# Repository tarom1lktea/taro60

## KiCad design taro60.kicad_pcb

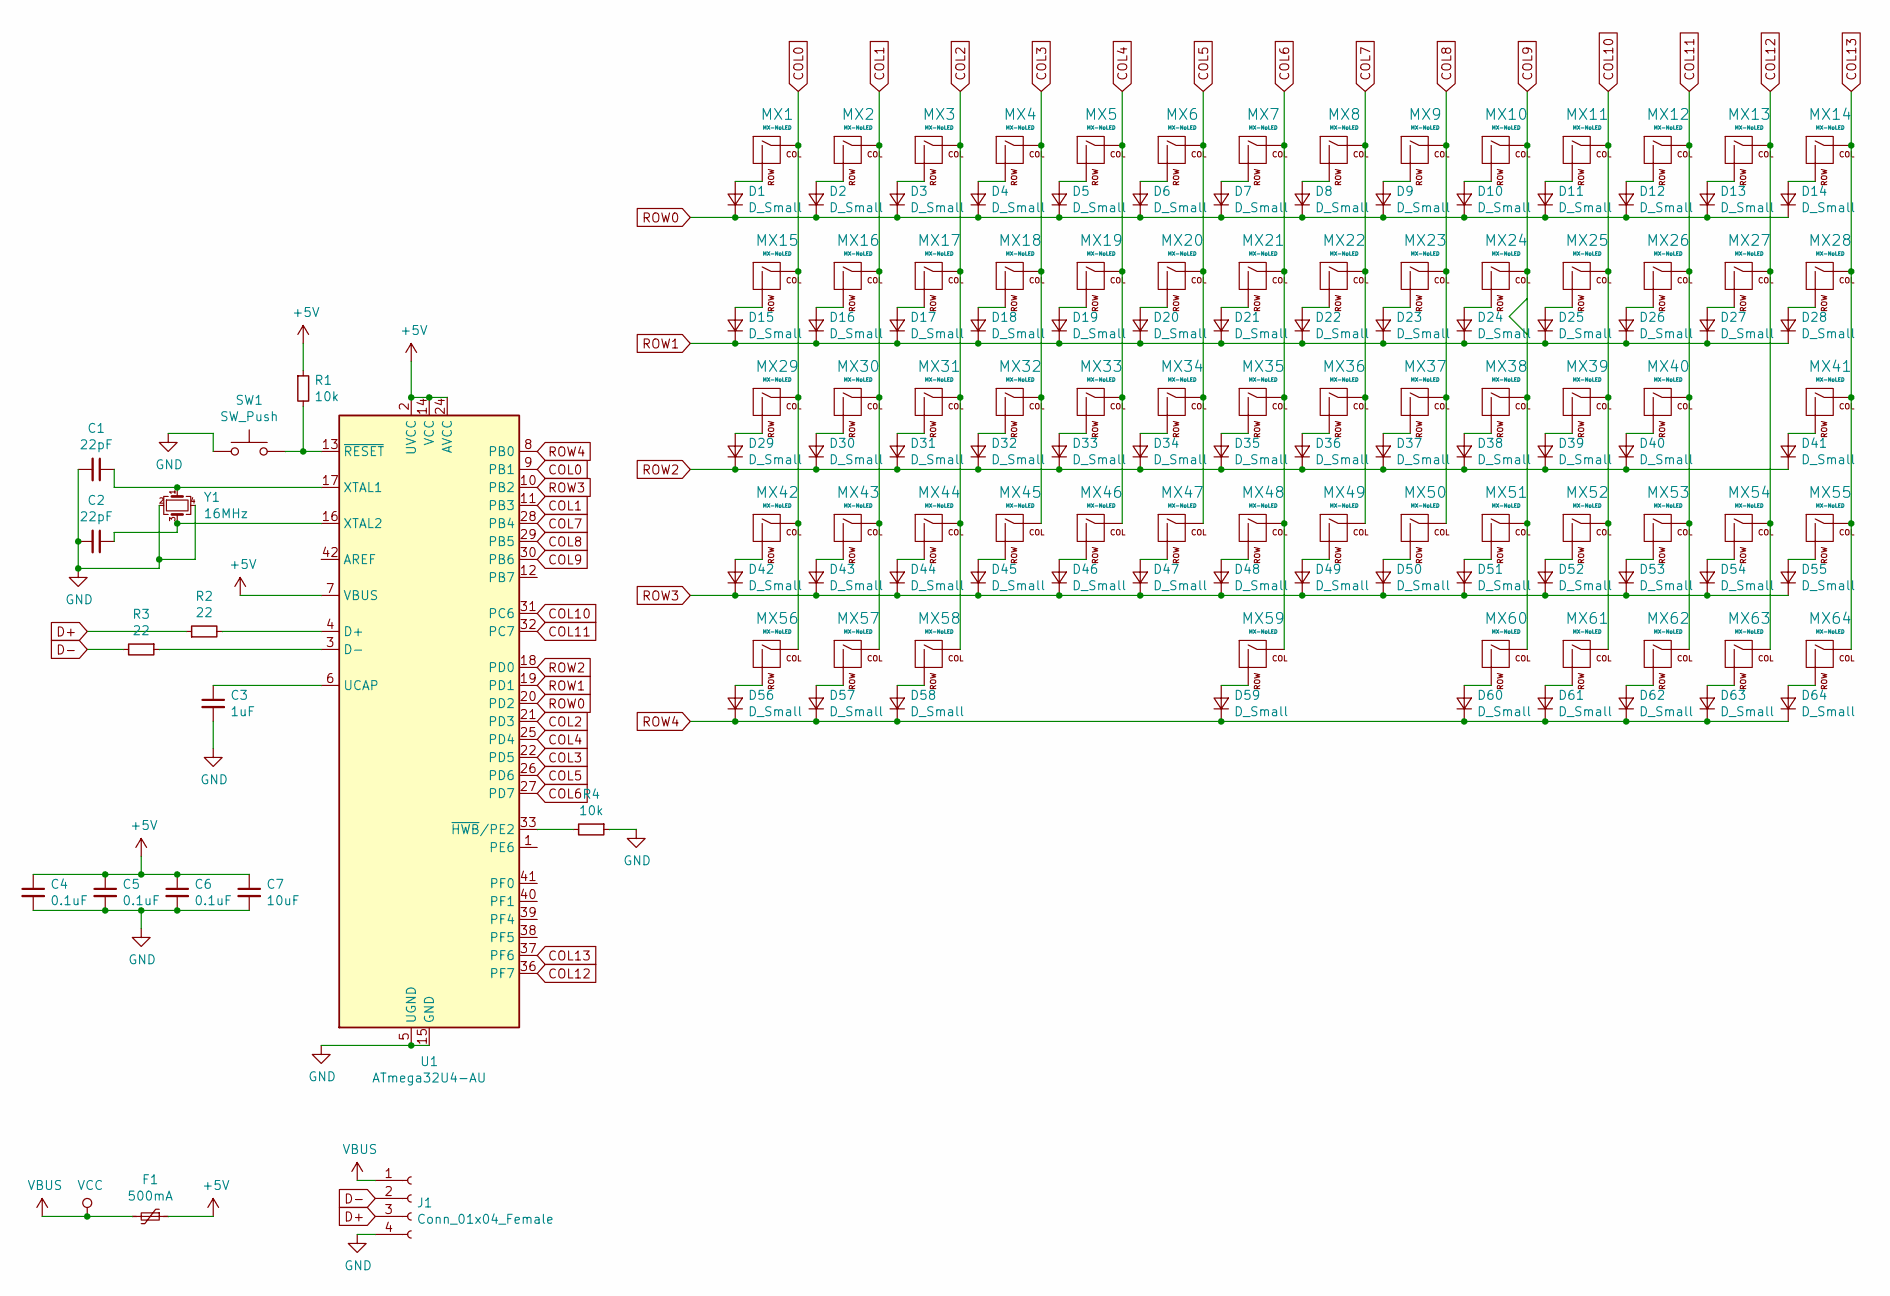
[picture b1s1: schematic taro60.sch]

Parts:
C1, C2: 22pF; C_0805_2012Metric
C3: 1uF; C_0805_2012Metric
C4, C5, C6: 0.1uF; C_0805_2012Metric
C7: 10uF; C_0805_2012Metric
D1, D2, D3, D4, D5, D6, D7, D8, D9, D10, D11, D12, D13, D14, D15, D16, D17, D18, D19, D20, D21, D22, D23, D24, D25, D26, D27, D28, D29, D30, D31, D32, D33, D34, D35, D36, D37, D38, D39, D40, D41, D42, D43, D44, D45, D46, D47, D48, D49, D50, D51, D52, D53, D54, D55, D56, D57, D58, D59, D60, D61, D62, D63, D64: D_Small; D_SOD-123
F1: 500mA; Fuse_1206_3216Metric
J1: Conn_01x04_Female; Molex_CLIK-Mate_502382-0470_1x04-1MP_P1.25mm_Vertical
MX1, MX2, MX3, MX4, MX5, MX6, MX7, MX8, MX9, MX10, MX11, MX12, MX13, MX16, MX17, MX18, MX19, MX20, MX21, MX22, MX23, MX24, MX25, MX26, MX27, MX30, MX31, MX32, MX33, MX34, MX35, MX36, MX37, MX38, MX39, MX40, MX43, MX44, MX45, MX46, MX47, MX48, MX49, MX50, MX51, MX52, MX53, MX54, MX55, MX60, MX61, MX62, MX63, MX64: MX-NoLED; MX-1U-NoLED
MX14, MX42: MX-NoLED; MX-2U-NoLED
MX15, MX28: MX-NoLED; MX-1.5U-NoLED
MX29: MX-NoLED; MX-1.75U-NoLED
MX41: MX-NoLED; MX-2.25U-NoLED
MX56, MX57, MX58: MX-NoLED; MX-1.25U-NoLED
MX59: MX-NoLED; MX-6.25U-ReversedStabilizers-NoLED
R1, R4: 10k; R_0805_2012Metric
R2, R3: 22; R_0805_2012Metric
SW1: SW_Push; SKQG-1155865
U1: ATmega32U4-AU; TQFP-44_10x10mm_P0.8mm
Y1: 16MHz; Crystal_SMD_3225-4Pin_3.2x2.5mm

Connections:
+5V: C4.1, C5.1, C6.1, C7.1, F1.1, R1.1, U1.2 (UVCC), U1.7 (VBUS), U1.14 (VCC), U1.24 (AVCC), U1.34 (VCC), U1.44 (AVCC)
COL0: MX1.1 (COL), MX15.1 (COL), MX29.1 (COL), MX42.1 (COL), MX56.1 (COL), U1.9 (PB1)
COL1: MX2.1 (COL), MX16.1 (COL), MX30.1 (COL), MX43.1 (COL), MX57.1 (COL), U1.11 (PB3)
COL2: MX3.1 (COL), MX17.1 (COL), MX31.1 (COL), MX44.1 (COL), MX58.1 (COL), U1.21 (PD3)
COL3: MX4.1 (COL), MX18.1 (COL), MX32.1 (COL), MX45.1 (COL), U1.22 (PD5)
COL4: MX5.1 (COL), MX19.1 (COL), MX33.1 (COL), MX46.1 (COL), U1.25 (PD4)
COL5: MX6.1 (COL), MX20.1 (COL), MX34.1 (COL), MX47.1 (COL), U1.26 (PD6)
COL6: MX7.1 (COL), MX21.1 (COL), MX35.1 (COL), MX48.1 (COL), MX59.1 (COL), U1.27 (PD7)
COL7: MX8.1 (COL), MX22.1 (COL), MX36.1 (COL), MX49.1 (COL), U1.28 (PB4)
COL8: MX9.1 (COL), MX23.1 (COL), MX37.1 (COL), MX50.1 (COL), U1.29 (PB5)
COL9: MX10.1 (COL), MX24.1 (COL), MX38.1 (COL), MX51.1 (COL), MX60.1 (COL), U1.30 (PB6)
COL10: MX11.1 (COL), MX25.1 (COL), MX39.1 (COL), MX52.1 (COL), MX61.1 (COL), U1.31 (PC6)
COL11: MX12.1 (COL), MX26.1 (COL), MX40.1 (COL), MX53.1 (COL), MX62.1 (COL), U1.32 (PC7)
COL12: MX13.1 (COL), MX27.1 (COL), MX54.1 (COL), MX63.1 (COL), U1.36 (PF7)
COL13: MX14.1 (COL), MX28.1 (COL), MX41.1 (COL), MX55.1 (COL), MX64.1 (COL), U1.37 (PF6)
D+: J1.3, R2.1
D-: J1.2, R3.2
GND: C1.2, C2.2, C3.2, C4.2, C5.2, C6.2, C7.2, J1.4, R4.1, SW1.1, U1.5 (UGND), U1.15 (GND), U1.23 (GND), U1.35 (GND), U1.43 (GND), Y1.2, Y1.4
unnamed: C1.1, U1.17 (XTAL1), Y1.1
unnamed: C2.1, U1.16 (XTAL2), Y1.3
unnamed: C3.1, U1.6 (UCAP)
unnamed: D1.2 (A), MX1.2 (ROW)
unnamed: D2.2 (A), MX2.2 (ROW)
unnamed: D3.2 (A), MX3.2 (ROW)
unnamed: D4.2 (A), MX4.2 (ROW)
unnamed: D5.2 (A), MX5.2 (ROW)
unnamed: D6.2 (A), MX6.2 (ROW)
unnamed: D7.2 (A), MX7.2 (ROW)
unnamed: D8.2 (A), MX8.2 (ROW)
unnamed: D9.2 (A), MX9.2 (ROW)
unnamed: D10.2 (A), MX10.2 (ROW)
unnamed: D11.2 (A), MX11.2 (ROW)
unnamed: D12.2 (A), MX12.2 (ROW)
unnamed: D13.2 (A), MX13.2 (ROW)
unnamed: D14.2 (A), MX14.2 (ROW)
unnamed: D15.2 (A), MX15.2 (ROW)
unnamed: D16.2 (A), MX16.2 (ROW)
unnamed: D17.2 (A), MX17.2 (ROW)
unnamed: D18.2 (A), MX18.2 (ROW)
unnamed: D19.2 (A), MX19.2 (ROW)
unnamed: D20.2 (A), MX20.2 (ROW)
unnamed: D21.2 (A), MX21.2 (ROW)
unnamed: D22.2 (A), MX22.2 (ROW)
unnamed: D23.2 (A), MX23.2 (ROW)
unnamed: D24.2 (A), MX24.2 (ROW)
unnamed: D25.2 (A), MX25.2 (ROW)
unnamed: D26.2 (A), MX26.2 (ROW)
unnamed: D27.2 (A), MX27.2 (ROW)
unnamed: D28.2 (A), MX28.2 (ROW)
unnamed: D29.2 (A), MX29.2 (ROW)
unnamed: D30.2 (A), MX30.2 (ROW)
unnamed: D31.2 (A), MX31.2 (ROW)
unnamed: D32.2 (A), MX32.2 (ROW)
unnamed: D33.2 (A), MX33.2 (ROW)
unnamed: D34.2 (A), MX34.2 (ROW)
unnamed: D35.2 (A), MX35.2 (ROW)
unnamed: D36.2 (A), MX36.2 (ROW)
unnamed: D37.2 (A), MX37.2 (ROW)
unnamed: D38.2 (A), MX38.2 (ROW)
unnamed: D39.2 (A), MX39.2 (ROW)
unnamed: D40.2 (A), MX40.2 (ROW)
unnamed: D41.2 (A), MX41.2 (ROW)
unnamed: D42.2 (A), MX42.2 (ROW)
unnamed: D43.2 (A), MX43.2 (ROW)
unnamed: D44.2 (A), MX44.2 (ROW)
unnamed: D45.2 (A), MX45.2 (ROW)
unnamed: D46.2 (A), MX46.2 (ROW)
unnamed: D47.2 (A), MX47.2 (ROW)
unnamed: D48.2 (A), MX48.2 (ROW)
unnamed: D49.2 (A), MX49.2 (ROW)
unnamed: D50.2 (A), MX50.2 (ROW)
unnamed: D51.2 (A), MX51.2 (ROW)
unnamed: D52.2 (A), MX52.2 (ROW)
unnamed: D53.2 (A), MX53.2 (ROW)
unnamed: D54.2 (A), MX54.2 (ROW)
unnamed: D55.2 (A), MX55.2 (ROW)
unnamed: D56.2 (A), MX56.2 (ROW)
unnamed: D57.2 (A), MX57.2 (ROW)
unnamed: D58.2 (A), MX58.2 (ROW)
unnamed: D59.2 (A), MX59.2 (ROW)
unnamed: D60.2 (A), MX60.2 (ROW)
unnamed: D61.2 (A), MX61.2 (ROW)
unnamed: D62.2 (A), MX62.2 (ROW)
unnamed: D63.2 (A), MX63.2 (ROW)
unnamed: D64.2 (A), MX64.2 (ROW)
unnamed: R1.2, SW1.2, U1.13 (~RESET)
unnamed: R2.2, U1.4 (D+)
unnamed: R3.1, U1.3 (D-)
unnamed: R4.2, U1.33 (~HWB~/PE2)
ROW0: D1.1 (K), D2.1 (K), D3.1 (K), D4.1 (K), D5.1 (K), D6.1 (K), D7.1 (K), D8.1 (K), D9.1 (K), D10.1 (K), D11.1 (K), D12.1 (K), D13.1 (K), D14.1 (K), U1.20 (PD2)
ROW1: D15.1 (K), D16.1 (K), D17.1 (K), D18.1 (K), D19.1 (K), D20.1 (K), D21.1 (K), D22.1 (K), D23.1 (K), D24.1 (K), D25.1 (K), D26.1 (K), D27.1 (K), D28.1 (K), U1.19 (PD1)
ROW2: D29.1 (K), D30.1 (K), D31.1 (K), D32.1 (K), D33.1 (K), D34.1 (K), D35.1 (K), D36.1 (K), D37.1 (K), D38.1 (K), D39.1 (K), D40.1 (K), D41.1 (K), U1.18 (PD0)
ROW3: D42.1 (K), D43.1 (K), D44.1 (K), D45.1 (K), D46.1 (K), D47.1 (K), D48.1 (K), D49.1 (K), D50.1 (K), D51.1 (K), D52.1 (K), D53.1 (K), D54.1 (K), D55.1 (K), U1.10 (PB2)
ROW4: D56.1 (K), D57.1 (K), D58.1 (K), D59.1 (K), D60.1 (K), D61.1 (K), D62.1 (K), D63.1 (K), D64.1 (K), U1.8 (PB0)
VBUS: F1.2, J1.1

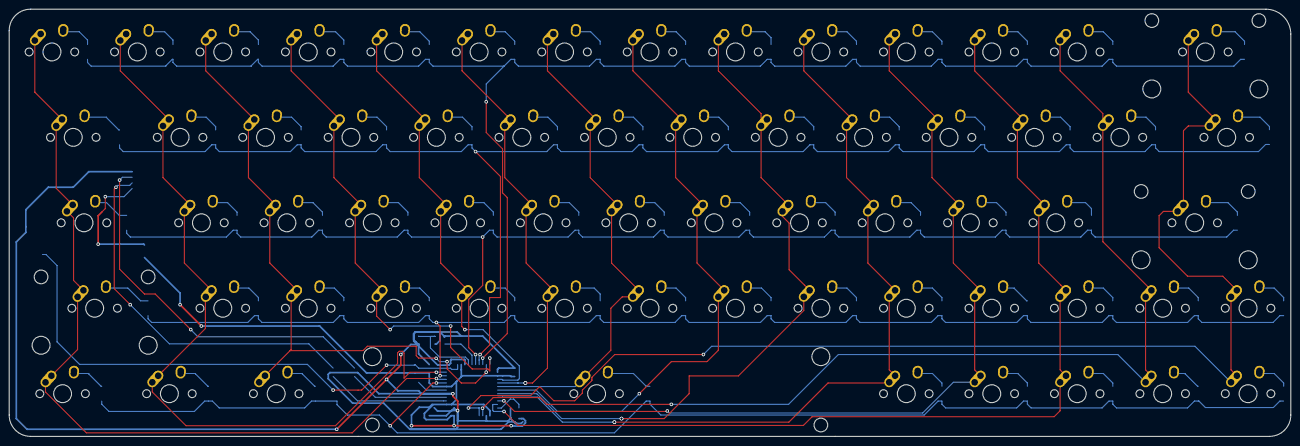
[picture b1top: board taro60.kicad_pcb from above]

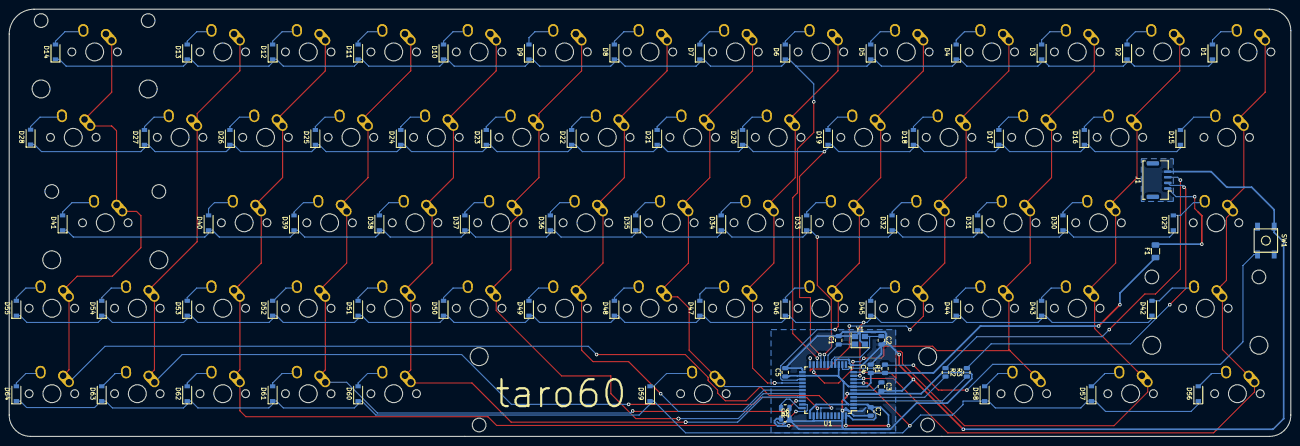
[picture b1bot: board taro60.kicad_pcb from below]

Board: 2 copper layers, 285.8 x 95.2 mm, 144 parts (80 on the bottom side), 95 nets.

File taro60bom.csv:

Comment,Designator,Footprint,Quantity
Conn_01x04_Female,J1,Molex_CLIK-Mate_502382-0470_1x04-1MP_P1.25mm_Vertical,1
MX-NoLED,"MX2,MX12,MX64,MX63,MX62,MX61,MX60,MX55,MX54,MX53,MX52,MX51,MX50,MX49,MX48,MX47,MX46,MX45,MX44,MX43,MX40,MX39,MX38,MX37,MX36,MX35,MX34,MX33,MX32,MX31,MX30,MX27,MX26,MX25,MX24,MX23,MX22,MX21,MX20,MX19,MX18,MX17,MX16,MX13,MX11,MX10,MX9,MX8,MX7,MX6,MX5,MX4,MX3,MX1",MX-1U-NoLED,54
MX-NoLED,MX59,MX-6.25U-ReversedStabilizers-NoLED,1
16MHz,Y1,Crystal_SMD_3225-4Pin_3.2x2.5mm,1
ATmega32U4-AU,U1,TQFP-44_10x10mm_P0.8mm,1
SW_Push,SW1,SKQG-1155865,1
10k,"R4,R1",R_0805_2012Metric,2
22,"R3,R2",R_0805_2012Metric,2
MX-NoLED,"MX58,MX57,MX56",MX-1.25U-NoLED,3
MX-NoLED,"MX42,MX14",MX-2U-NoLED,2
MX-NoLED,MX41,MX-2.25U-NoLED,1
MX-NoLED,MX29,MX-1.75U-NoLED,1
MX-NoLED,"MX28,MX15",MX-1.5U-NoLED,2
500mA,F1,Fuse_1206_3216Metric,1
D_Small,"D64,D63,D62,D61,D60,D59,D58,D57,D56,D55,D54,D53,D52,D51,D50,D49,D48,D47,D46,D45,D44,D43,D42,D41,D40,D39,D38,D37,D36,D35,D34,D33,D32,D31,D30,D29,D28,D27,D26,D25,D24,D23,D22,D21,D20,D19,D18,D17,D16,D15,D14,D13,D12,D11,D10,D9,D8,D7,D6,D5,D4,D3,D2,D1",D_SOD-123,64
10uF,C7,C_0805_2012Metric,1
0.1uF,"C6,C5,C4",C_0805_2012Metric,3
1uF,C3,C_0805_2012Metric,1
22pF,"C2,C1",C_0805_2012Metric,2
